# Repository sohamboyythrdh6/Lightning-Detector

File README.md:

# Lightning-Detector
Its a detector that can detect lightning strikes 

| Component | Purpose | Qty | Cost (USD) | Distributor |
|-----------|---------|-----|------------|-------------|
| Seeed Studio XIAO ESP32S3 | Main controller of the project | 1 | $12.00 | Robu.in |
| DFRobot Gravity Lightning Distance Sensor | Detects lightning activity | 1 | $25.00 | Robu.in |
| Waveshare 1.54" E-Ink Display Module | Displays visual information | 1 | $20.00 | Amazon.in |
| 3.7V 450mAh 1S LiPo Battery | Powers the project | 1 | $3.13 | Robu.in |
| LiPo Charger with USB-C | Charges the LiPo battery | 1 | $3.00 | Robu.in |
| CL7525A-CLDZ Passive Buzzer | Provides an audible warning | 1 | $1.00 | Robu.in |
| BC547 SMD Transistor | Controls the warning circuit | 1 | $1.00 | Robu.in |
| 0805 Red SMD LED | Provides a visual warning | 1 | $1.00 | Robu.in |
| 330Ω SMD Resistor | Limits LED current | 1 | $1.00 | Robu.in |
| 1kΩ SMD Resistor | Limits current | 1 | $1.00 | Robu.in |
| SMD Slide Switch | Turns the project ON/OFF | 1 | $1.00 | Robu.in |
| Custom PCB | Mounts and connects all components | 1 | $4.00 | JLCPCB |
| Delivery Charges | Shipping costs | 1 | $12.00 | — |

**💰 Total Estimated Cost: $90 USD**

And with just few steps you can also able to build this and it might save your live
to build this detector you need to get all the parts listed in the BOM and the PCB the gerber file is also given in the production file 

After getting all the components solder all the components and you are done now whenever you scenic some lightning strikes just turn on this device by the switch and you can see the distance of the strikes and how strong the strikes are also it can count theme.
I think this device can warn you by sowing the strength of the strikes.

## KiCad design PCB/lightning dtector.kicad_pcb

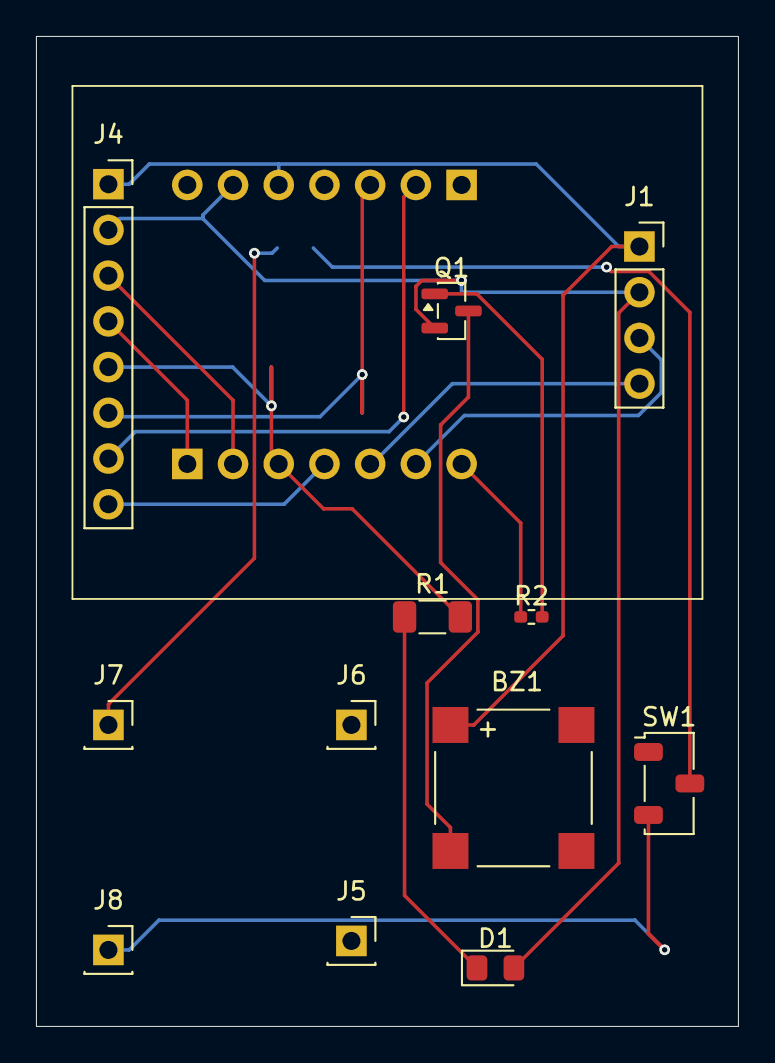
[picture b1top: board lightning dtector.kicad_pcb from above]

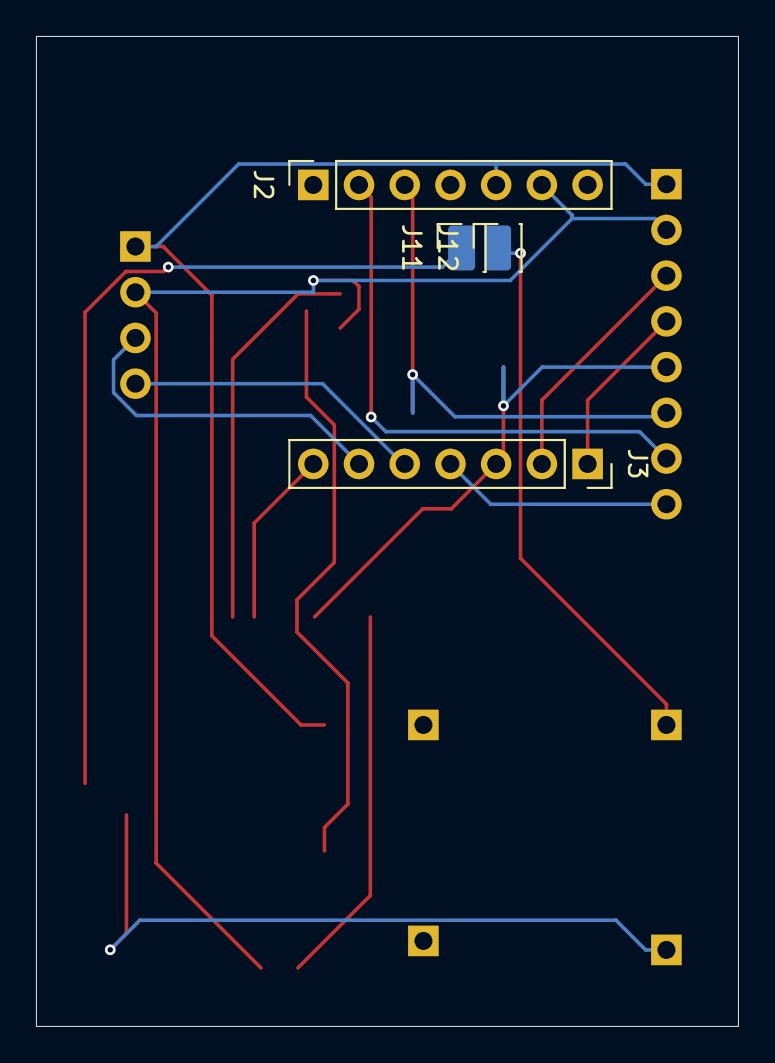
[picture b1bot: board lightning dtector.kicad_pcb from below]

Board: 2 copper layers, 39.0 x 55.0 mm, 16 parts (4 on the bottom side), 17 nets.

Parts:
BZ1: Buzzer; PUIAudio_SMT_0825_S_4_R
D1: LED; LED_0805_2012Metric_Pad1.15x1.40mm_HandSolder
J1: lightning sensor; PinSocket_1x04_P2.54mm_Vertical
J2: right; PinSocket_1x07_P2.54mm_Vertical
J3: left; PinSocket_1x07_P2.54mm_Vertical
J4: E ink display; PinSocket_1x08_P2.54mm_Vertical
J5: IN+; PinSocket_1x01_P2.54mm_Vertical
J6: IN-; PinSocket_1x01_P2.54mm_Vertical
J7: BAT-; PinSocket_1x01_P2.54mm_Vertical
J8: BAT+; PinSocket_1x01_P2.54mm_Vertical
J11: +; PinSocket_1x01_P2.54mm_Vertical
J12: -; PinSocket_1x01_P2.54mm_Vertical
Q1: BC547; SOT-23
R1: 330; R_1206_3216Metric_Pad1.30x1.75mm_HandSolder
R2: 1k; R_0402_1005Metric_Pad0.72x0.64mm_HandSolder
SW1: SW_Nidec_CAS-120A1; Nidec_Copal_CAS-120A

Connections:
/+: BZ1.1 (+), J1.1, J2.5, J4.1
/-: D1.2 (A), J1.2, J2.6, J4.2, Q1.2 (B)
/BUSY: J3.1, J4.4
/C: J1.3, J3.6
/CS: J3.4, J4.8
/D: J1.4, J3.5
/D1: J3.2, J4.3
/D2: J3.3, J4.5, R1.2
/D6: J3.7, R2.1
/D8: J2.2, J4.7
/D9: J2.3, J4.6
unnamed: BZ1.2 (-), Q1.3 (E)
unnamed: D1.1 (K), R1.1
unnamed: J8.1 (Pin_1_1), SW1.3 (A)
unnamed: J11.1 (Pin_1_1), SW1.2 (B)
unnamed: J7.1 (Pin_1_1), J12.1 (Pin_1_1)
unnamed: Q1.1 (C), R2.2
